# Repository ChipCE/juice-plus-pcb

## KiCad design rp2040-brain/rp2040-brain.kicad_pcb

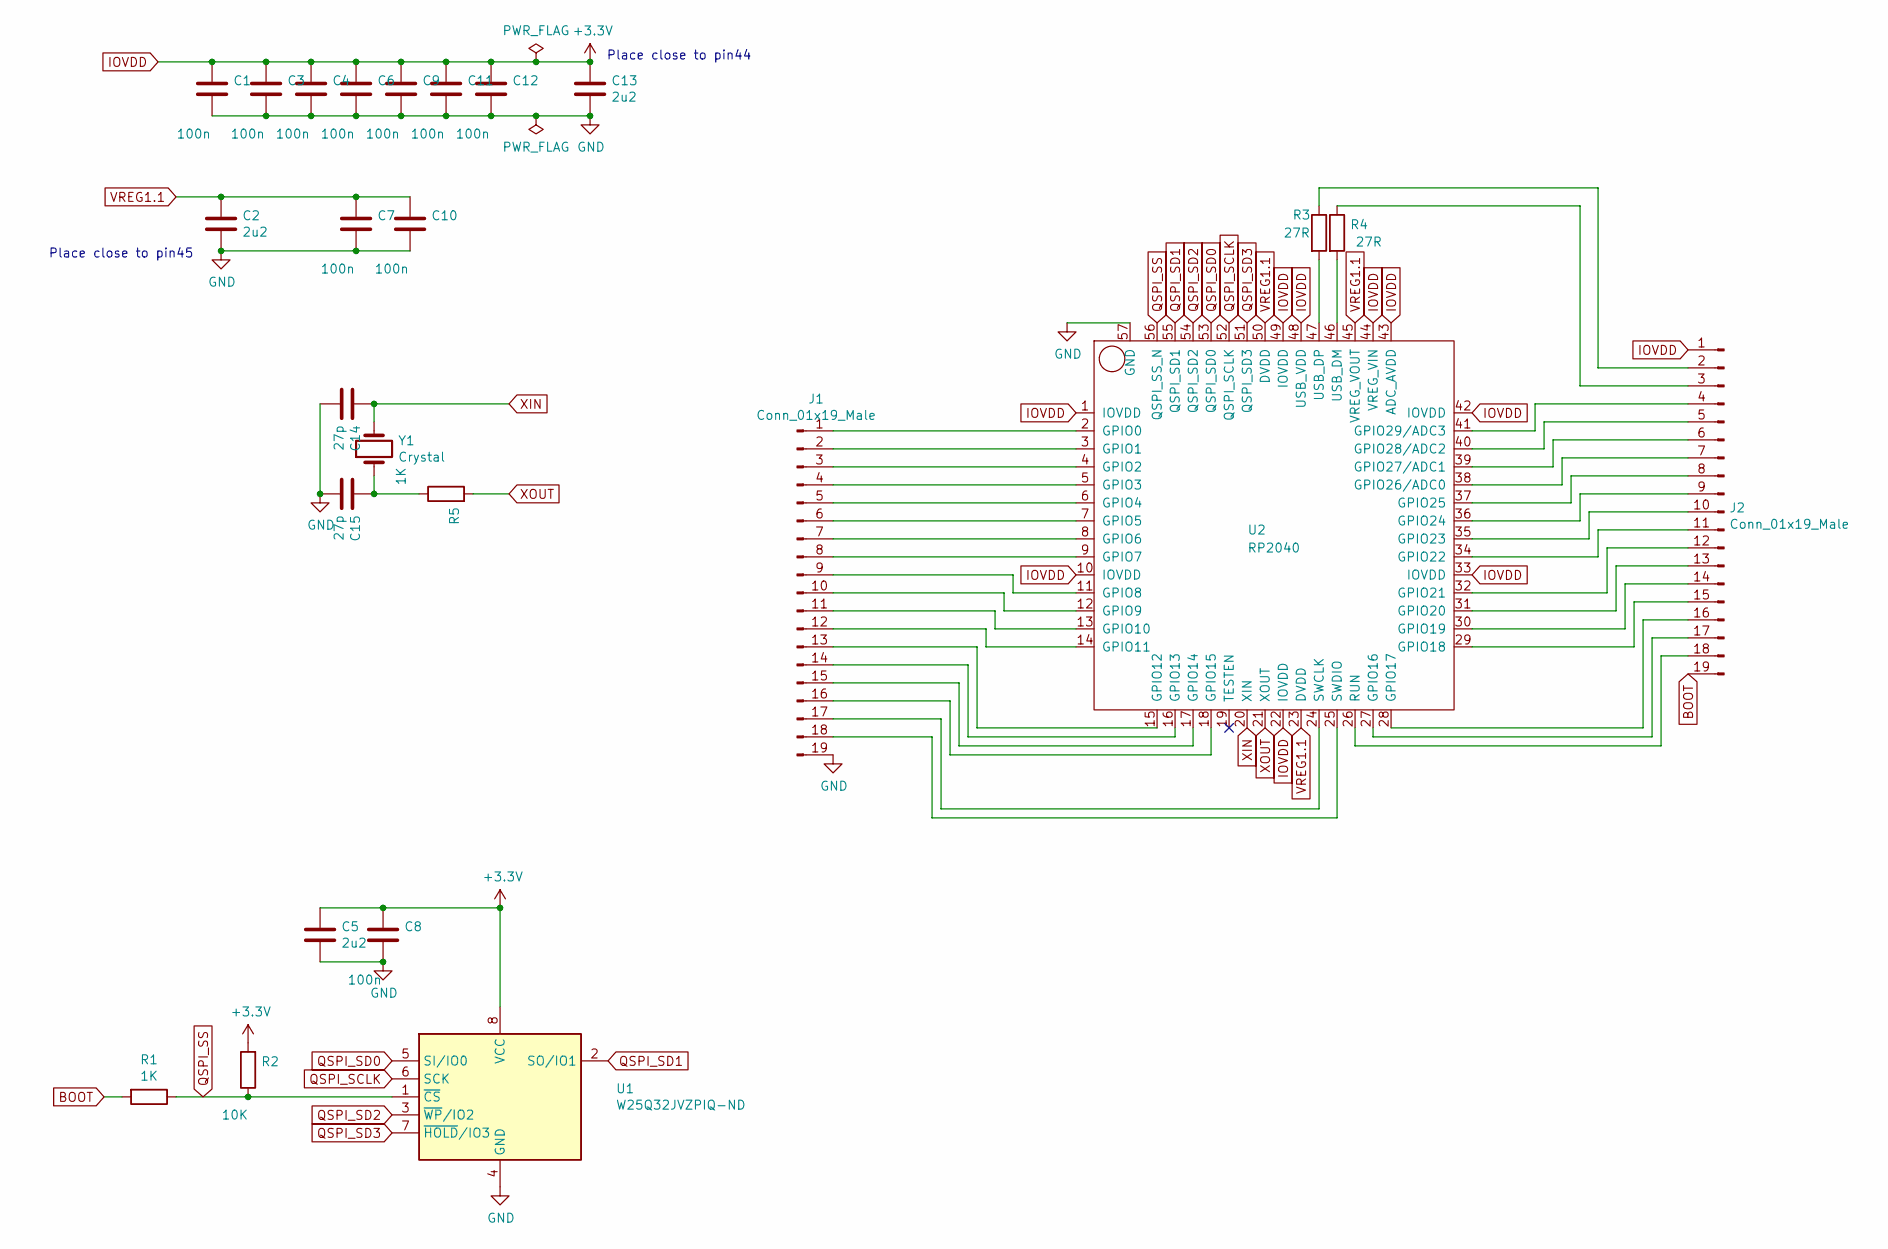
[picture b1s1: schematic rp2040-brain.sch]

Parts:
C1, C3, C4, C6, C7, C8, C9, C10, C11, C12: 100n; C_0603_1608Metric
C2, C5, C13: 2u2; C_0603_1608Metric
C14, C15: 27p; C_0603_1608Metric
J1, J2: Conn_01x19_Male; PinHeader_1x19_P1.27mm_Vertical
R1, R5: 1K; R_0603_1608Metric
R2: 10K; R_0603_1608Metric
R3, R4: 27R; R_0603_1608Metric
U1: W25Q32JVZPIQ-ND‎; WSON-8-1EP_6x5mm_P1.27mm_EP3.4x4mm
U2: RP2040; QFN-56-1EP_7x7mm_P0.4mm_EP5.7x5.7mm
Y1: Crystal; Crystal_SMD_5032-2Pin_5.0x3.2mm

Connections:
BOOT: J2.19, R1.2
GND: C1.2, C2.2, C3.2, C4.2, C5.2, C6.2, C7.2, C8.2, C9.2, C10.2, C11.2, C12.2, C13.2, C14.2, C15.2, J1.19, U1.4 (GND), U2.57 (GND)
IOVDD: C1.1, C3.1, C4.1, C5.1, C6.1, C8.1, C9.1, C11.1, C12.1, C13.1, J2.1, R2.2, U1.8 (VCC), U2.1 (IOVDD), U2.10 (IOVDD), U2.22 (IOVDD), U2.33 (IOVDD), U2.42 (IOVDD), U2.43 (ADC_AVDD), U2.44 (VREG_VIN), U2.48 (USB_VDD), U2.49 (IOVDD)
unnamed: C15.1, R5.1, Y1.1
unnamed: J1.1, U2.2 (GPIO0)
unnamed: J1.2, U2.3 (GPIO1)
unnamed: J1.3, U2.4 (GPIO2)
unnamed: J1.4, U2.5 (GPIO3)
unnamed: J1.5, U2.6 (GPIO4)
unnamed: J1.6, U2.7 (GPIO5)
unnamed: J1.7, U2.8 (GPIO6)
unnamed: J1.8, U2.9 (GPIO7)
unnamed: J1.9, U2.11 (GPIO8)
unnamed: J1.10, U2.12 (GPIO9)
unnamed: J1.11, U2.13 (GPIO10)
unnamed: J1.12, U2.14 (GPIO11)
unnamed: J1.13, U2.15 (GPIO12)
unnamed: J1.14, U2.16 (GPIO13)
unnamed: J1.15, U2.17 (GPIO14)
unnamed: J1.16, U2.18 (GPIO15)
unnamed: J1.17, U2.24 (SWCLK)
unnamed: J1.18, U2.25 (SWDIO)
unnamed: J2.2, R3.1
unnamed: J2.3, R4.1
unnamed: J2.4, U2.41 (GPIO29/ADC3)
unnamed: J2.5, U2.40 (GPIO28/ADC2)
unnamed: J2.6, U2.39 (GPIO27/ADC1)
unnamed: J2.7, U2.38 (GPIO26/ADC0)
unnamed: J2.8, U2.37 (GPIO25)
unnamed: J2.9, U2.36 (GPIO24)
unnamed: J2.10, U2.35 (GPIO23)
unnamed: J2.11, U2.34 (GPIO22)
unnamed: J2.12, U2.32 (GPIO21)
unnamed: J2.13, U2.31 (GPIO20)
unnamed: J2.14, U2.30 (GPIO19)
unnamed: J2.15, U2.29 (GPIO18)
unnamed: J2.16, U2.28 (GPIO17)
unnamed: J2.17, U2.27 (GPIO16)
unnamed: J2.18, U2.26 (RUN)
unnamed: R3.2, U2.47 (USB_DP)
unnamed: R4.2, U2.46 (USB_DM)
QSPI_SCLK: U1.6 (SCK), U2.52 (QSPI_SCLK)
QSPI_SD0: U1.5 (SI/IO0), U2.53 (QSPI_SD0)
QSPI_SD1: U1.2 (SO/IO1), U2.55 (QSPI_SD1)
QSPI_SD2: U1.3 (~WP~/IO2), U2.54 (QSPI_SD2)
QSPI_SD3: U1.7 (~HOLD~/IO3), U2.51 (QSPI_SD3)
QSPI_SS: R1.1, R2.1, U1.1 (~CS), U2.56 (QSPI_SS_N)
VREG1.1: C2.1, C7.1, C10.1, U2.23 (DVDD), U2.45 (VREG_VOUT), U2.50 (DVDD)
XIN: C14.1, U2.20 (XIN), Y1.2
XOUT: R5.2, U2.21 (XOUT)

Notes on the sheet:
Place close to pin44
Place close to pin45

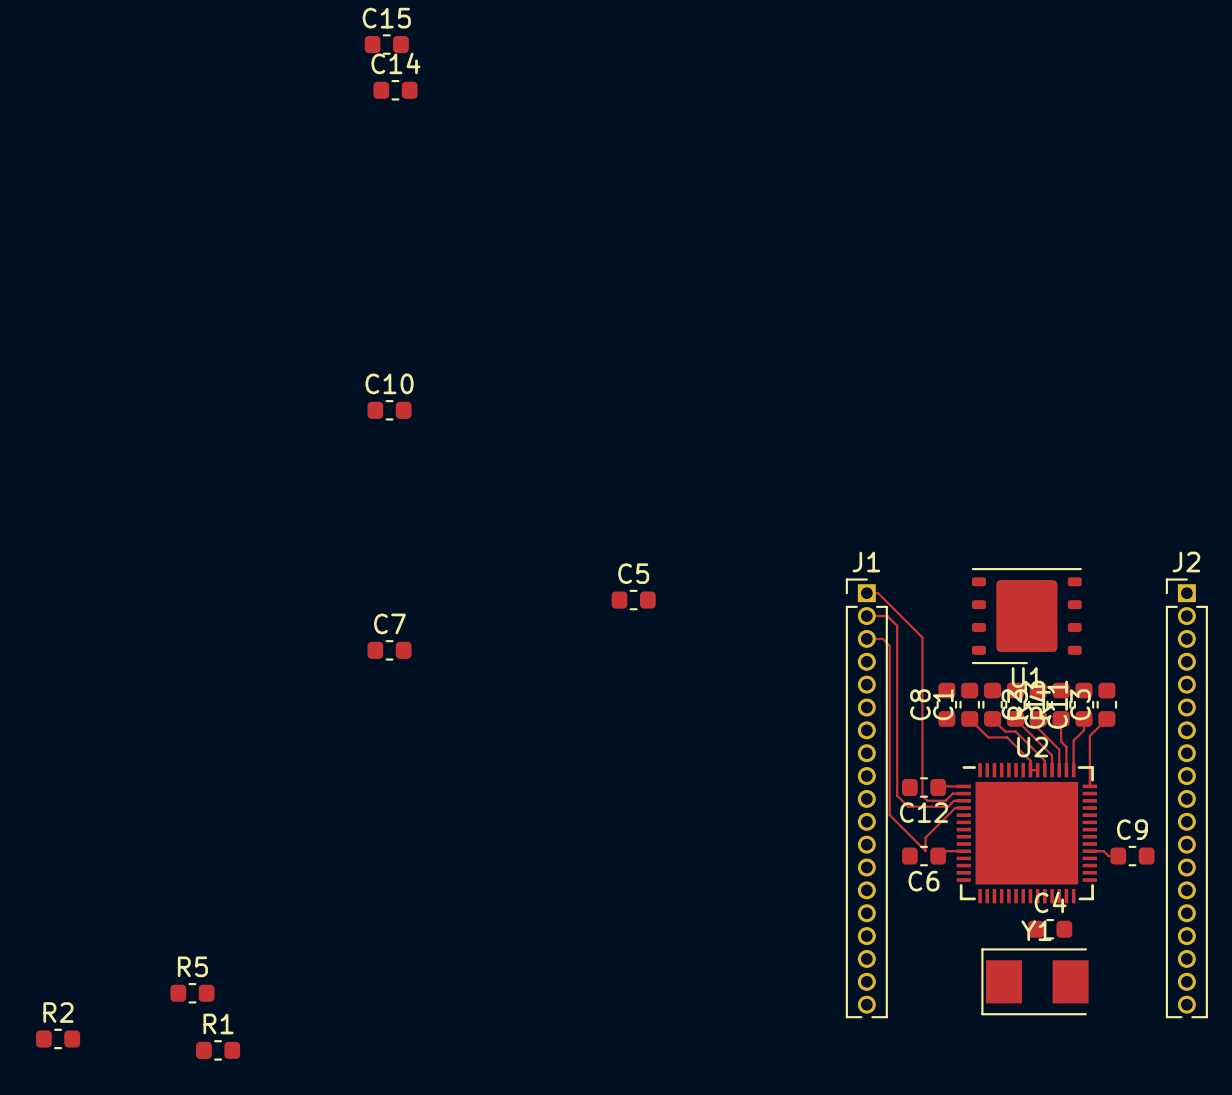
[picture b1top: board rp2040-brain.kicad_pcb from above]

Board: 4 copper layers, 25 parts (0 on the bottom side), 50 nets.

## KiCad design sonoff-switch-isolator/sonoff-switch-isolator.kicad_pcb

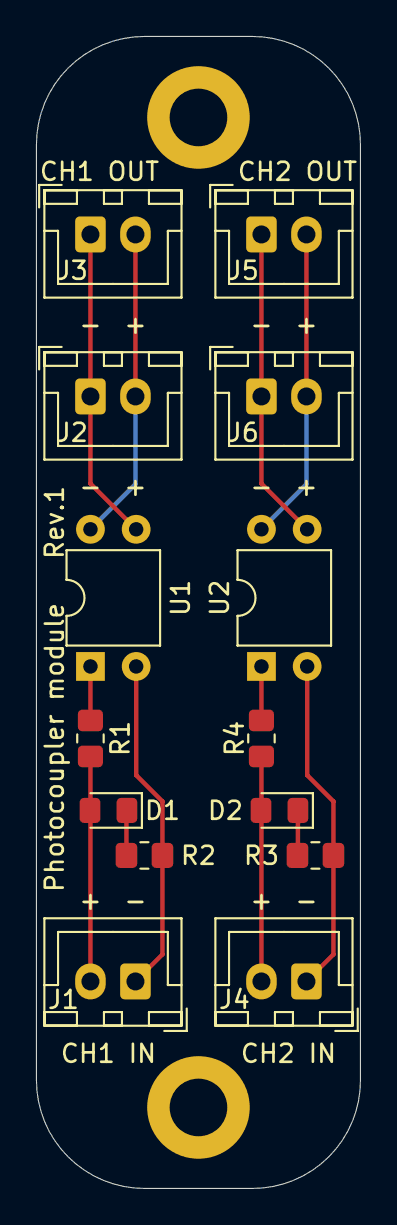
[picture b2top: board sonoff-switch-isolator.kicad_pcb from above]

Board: 2 copper layers, 18.0 x 64.0 mm, 14 parts (0 on the bottom side), 12 nets.

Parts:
D1, D2: LED; LED_0805_2012Metric_Pad1.15x1.40mm_HandSolder
J1, J2, J3, J4, J5, J6: Conn_01x02_Female; JST_XH_B2B-XH-A_1x02_P2.50mm_Vertical
R1, R2, R3, R4: R_US; R_0805_2012Metric_Pad1.20x1.40mm_HandSolder
U1, U2: SFH617A-1; DIP-4_W7.62mm

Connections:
unnamed: D1.1, R2.1
unnamed: D1.2, J1.2, R1.2
unnamed: D2.1, R3.1
unnamed: D2.2, J4.2, R4.2
unnamed: J1.1, R2.2, U1.2
unnamed: J2.1, J3.1, U1.3
unnamed: J2.2, J3.2, U1.4
unnamed: J4.1, R3.2, U2.2
unnamed: J5.1, J6.1, U2.3
unnamed: J5.2, J6.2, U2.4
unnamed: R1.1, U1.1
unnamed: R4.1, U2.1

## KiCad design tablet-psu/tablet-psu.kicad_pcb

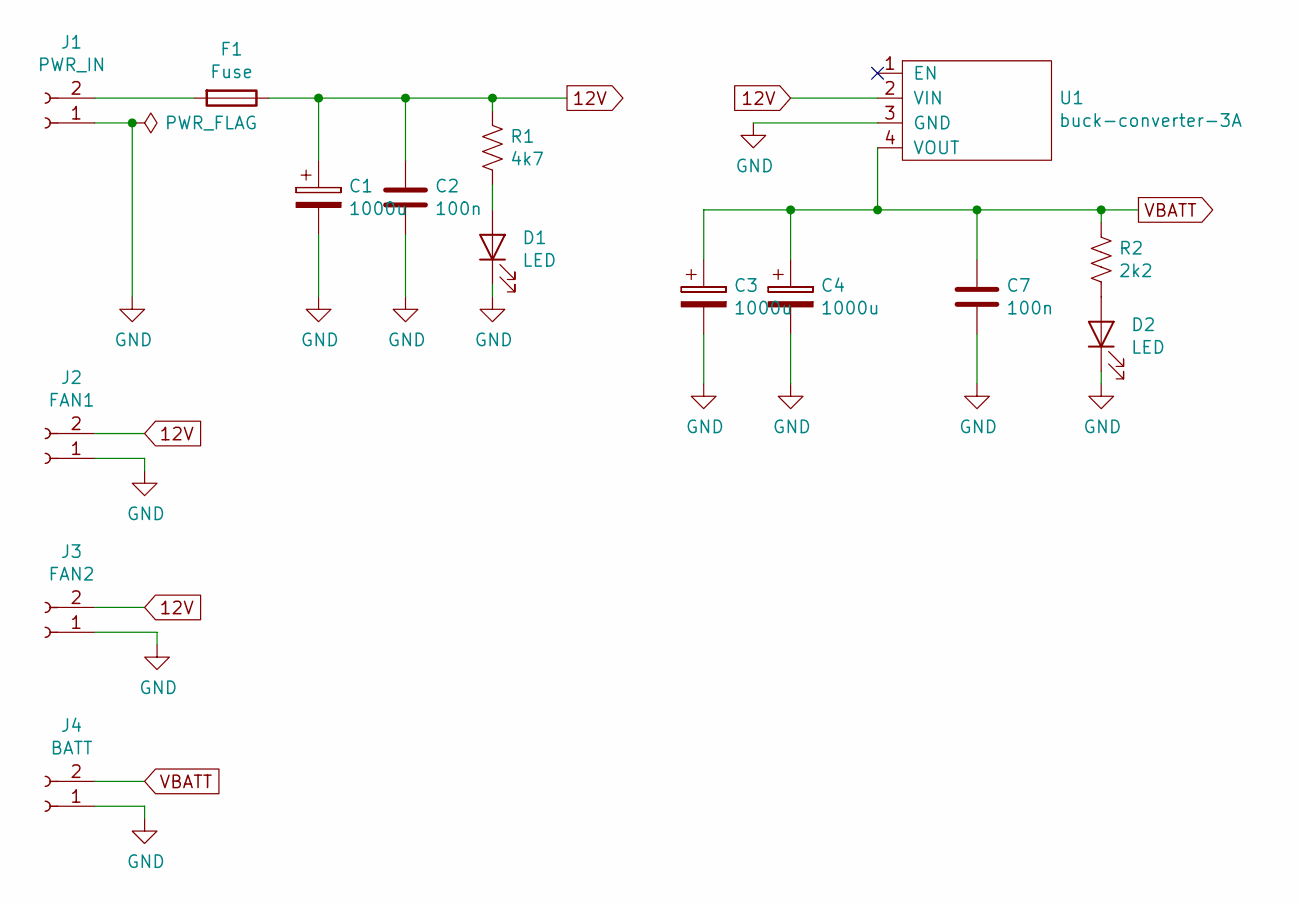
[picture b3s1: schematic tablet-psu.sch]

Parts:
C1, C3, C4: 1000u; capacitor-12p5-20mm
C2, C7: 100n; C_0805_2012Metric_Pad1.15x1.40mm_HandSolder
D1, D2: LED; LED_0805_2012Metric_Pad1.15x1.40mm_HandSolder
F1: Fuse; Fuse_2920_7451Metric_Pad2.10x5.45mm_HandSolder
J1: PWR_IN; JST_XH_S02B-XH-A_1x02_P2.50mm_Horizontal
J2: FAN1; JST_XH_S02B-XH-A_1x02_P2.50mm_Horizontal
J3: FAN2; JST_XH_S02B-XH-A_1x02_P2.50mm_Horizontal
J4: BATT; JST_XH_S02B-XH-A_1x02_P2.50mm_Horizontal
R1: 4k7; R_0805_2012Metric_Pad1.15x1.40mm_HandSolder
R2: 2k2; R_0805_2012Metric_Pad1.15x1.40mm_HandSolder
U1: buck-converter-3A; Buck-converter-3A

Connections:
12V: C1.1, C2.1, F1.1, J2.2, J3.2, R1.1, U1.2 (VIN)
GND: C1.2, C2.2, C3.2, C4.2, C7.2, D1.1 (K), D2.1 (K), J1.1, J2.1, J3.1, J4.1, U1.3 (GND)
unnamed: D1.2 (A), R1.2
unnamed: D2.2 (A), R2.1
unnamed: F1.2, J1.2
VBATT: C3.1, C4.1, C7.1, J4.2, R2.2, U1.4 (VOUT)

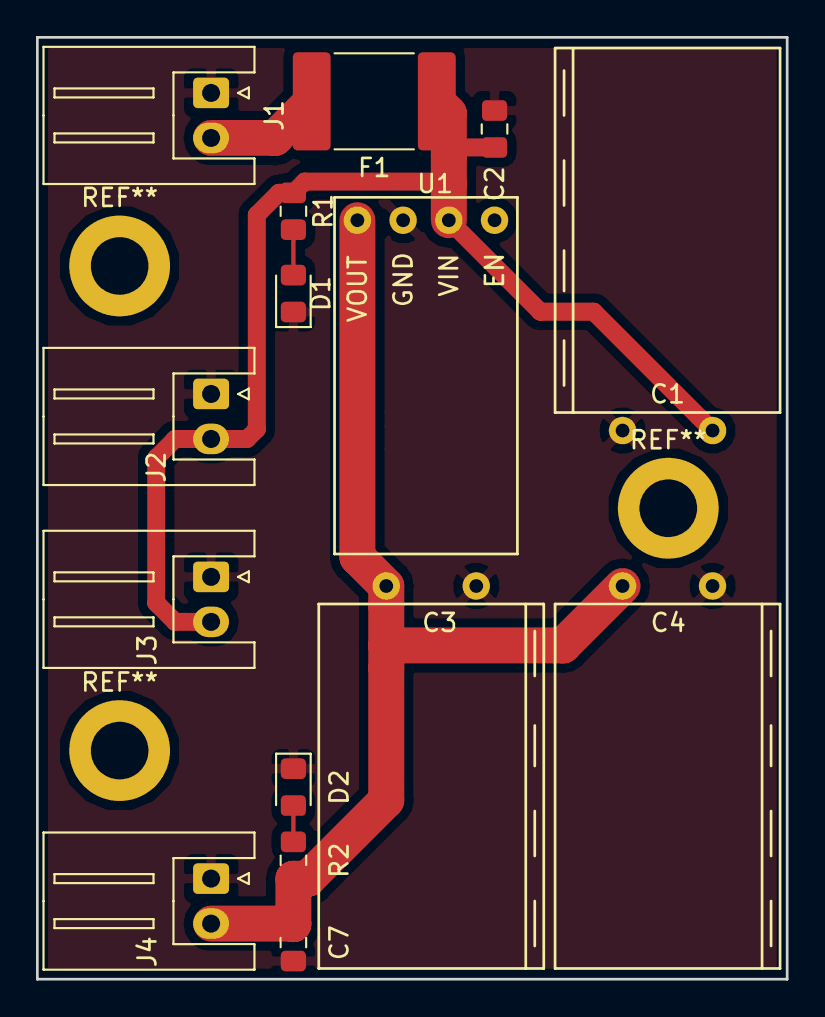
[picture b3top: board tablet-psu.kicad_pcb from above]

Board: 2 copper layers, 41.7 x 52.3 mm, 15 parts (0 on the bottom side), 6 nets.

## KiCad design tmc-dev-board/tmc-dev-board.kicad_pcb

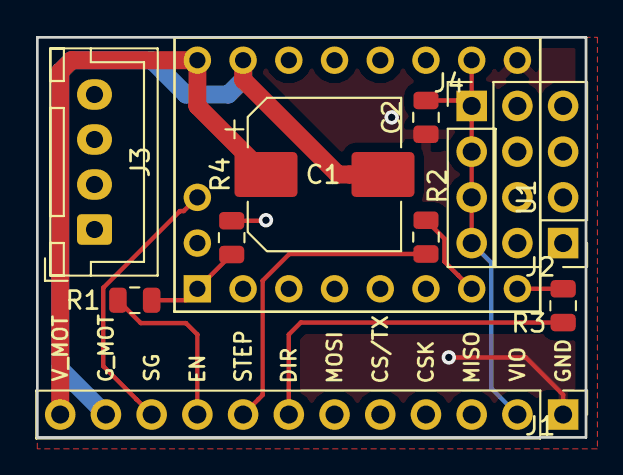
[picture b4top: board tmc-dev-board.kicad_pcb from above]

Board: 4 copper layers, 30.5 x 22.2 mm, 11 parts (0 on the bottom side), 23 nets.

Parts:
C1: 100u; CP_Elec_8x10
C2: 100n; C_0805_2012Metric
J1: Conn_01x12_Female; PinHeader_1x12_P2.54mm_Vertical
J2: UART/SPI_header; PinHeader_2x04_P2.54mm_Vertical
J3: Conn_01x04_Female; JST_XH_B04B-XH-A_1x04_P2.50mm_Vertical
J4: STEP/DIR_header; PinHeader_1x04_P2.54mm_Vertical
R1, R2, R3: 100R; R_0805_2012Metric
R4: 10K; R_0805_2012Metric
U1: TMC-step-stick

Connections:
CS: J2.4, U1.4
DIR: J1.7, R3.2
EN: J1.9, R1.2
GND: C2.2, J1.1, U1.9
G_MOT: C1.2, J1.11, U1.15
MISO: J2.8, U1.2
MOSI: J2.2, U1.5, U1.6
unnamed: J1.3, J2.7
unnamed: J1.4, J2.5
unnamed: J1.5, J2.3
unnamed: J1.6, J2.1
unnamed: J3.1, U1.11
unnamed: J3.2, U1.12
unnamed: J3.3, U1.13
unnamed: J3.4, U1.14
unnamed: R1.1, R4.1, U1.1
unnamed: R2.1, U1.7
unnamed: R3.1, U1.8
SCK: J2.6, U1.3
SG: J1.10, U1.18
STEP: J1.8, R2.2
VIO: C2.1, J1.2, J4.1, J4.2, J4.3, J4.4, R4.2, U1.10
V_MOT: C1.1, J1.12, U1.16

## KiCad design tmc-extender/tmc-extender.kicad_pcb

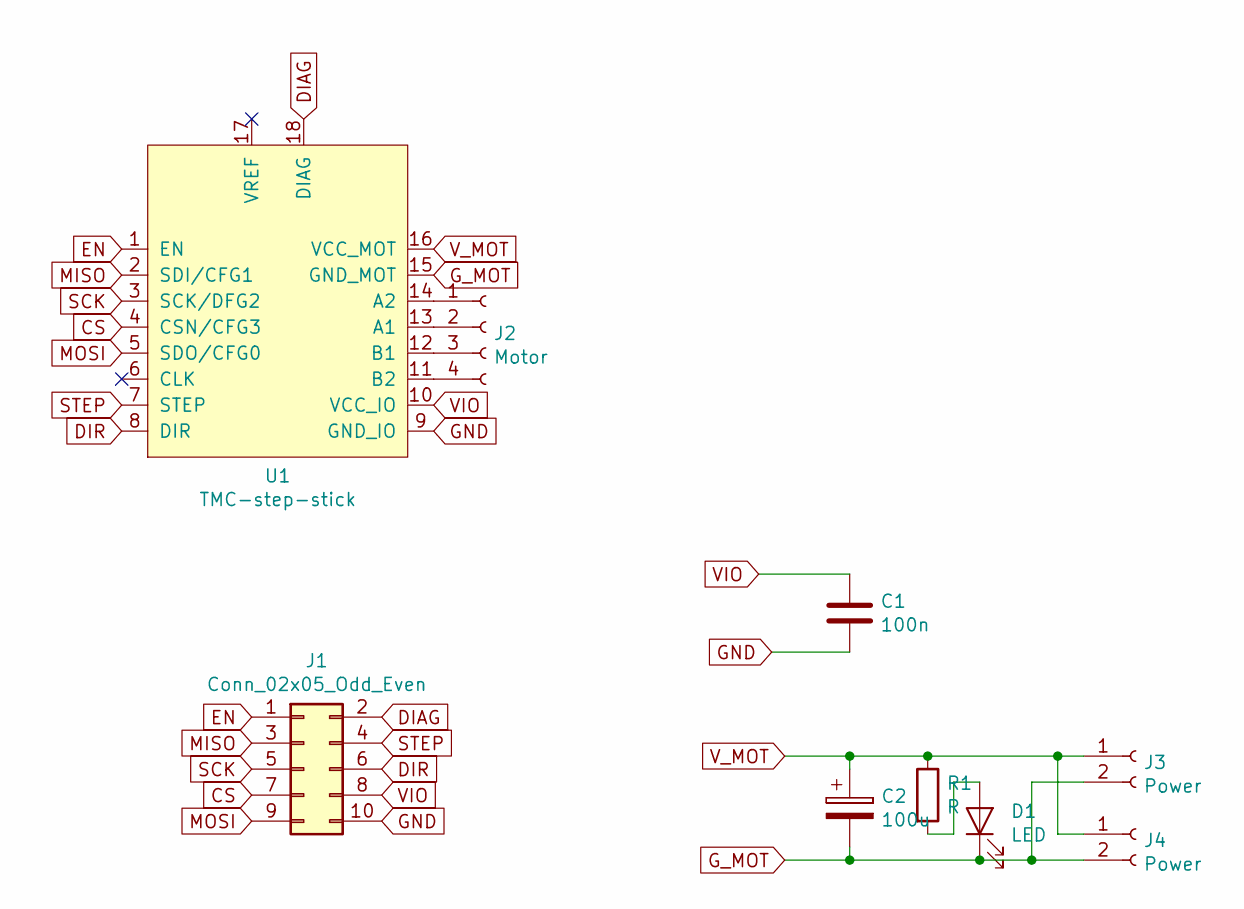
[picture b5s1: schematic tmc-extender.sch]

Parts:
C1: 100n; C_0805_2012Metric
C2: 100u; CP_Elec_10x10.5
D1: LED; LED_0805_2012Metric
J1: Conn_02x05_Odd_Even; IDC-Header_2x05_P2.54mm_Vertical
J2: Motor; JST_XH_B04B-XH-A_1x04_P2.50mm_Vertical
J3, J4: Power; JST_XH_B02B-XH-A_1x02_P2.50mm_Vertical
R1: R; R_0805_2012Metric
U1: TMC-step-stick

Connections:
CS: J1.7, U1.4 (CSN/CFG3)
DIAG: J1.2, U1.18 (DIAG)
DIR: J1.6, U1.8 (DIR)
EN: J1.1, U1.1 (EN)
GND: C1.2, J1.10, U1.9 (GND_IO)
G_MOT: C2.2, D1.1 (K), J3.2, J4.2, U1.15 (GND_MOT)
MISO: J1.3, U1.2 (SDI/CFG1)
MOSI: J1.9, U1.5 (SDO/CFG0)
unnamed: D1.2 (A), R1.2
unnamed: J2.1, U1.14 (A2)
unnamed: J2.2, U1.13 (A1)
unnamed: J2.3, U1.12 (B1)
unnamed: J2.4, U1.11 (B2)
SCK: J1.5, U1.3 (SCK/DFG2)
STEP: J1.4, U1.7 (STEP)
VIO: C1.1, J1.8, U1.10 (VCC_IO)
V_MOT: C2.1, J3.1, J4.1, R1.1, U1.16 (VCC_MOT)

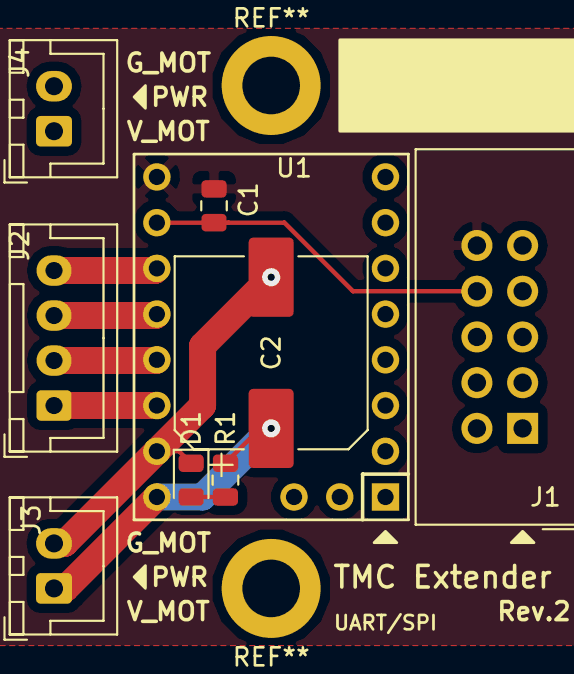
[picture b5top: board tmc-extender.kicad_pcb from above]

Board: 4 copper layers, 9 parts (0 on the bottom side), 17 nets.
